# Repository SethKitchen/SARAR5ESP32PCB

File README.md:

# SARAR5ESP32PCB
An IoT PCB integrating the ESP32 and ublox SARA-R5 . Allows for 5G Cellular, Wi-Fi, and Bluetooth in the same device with low form-factor.

This was an open source contibution sponsored by @hiperionio . Thanks so much! If you like what I'm doing please consider sponsoring as well!

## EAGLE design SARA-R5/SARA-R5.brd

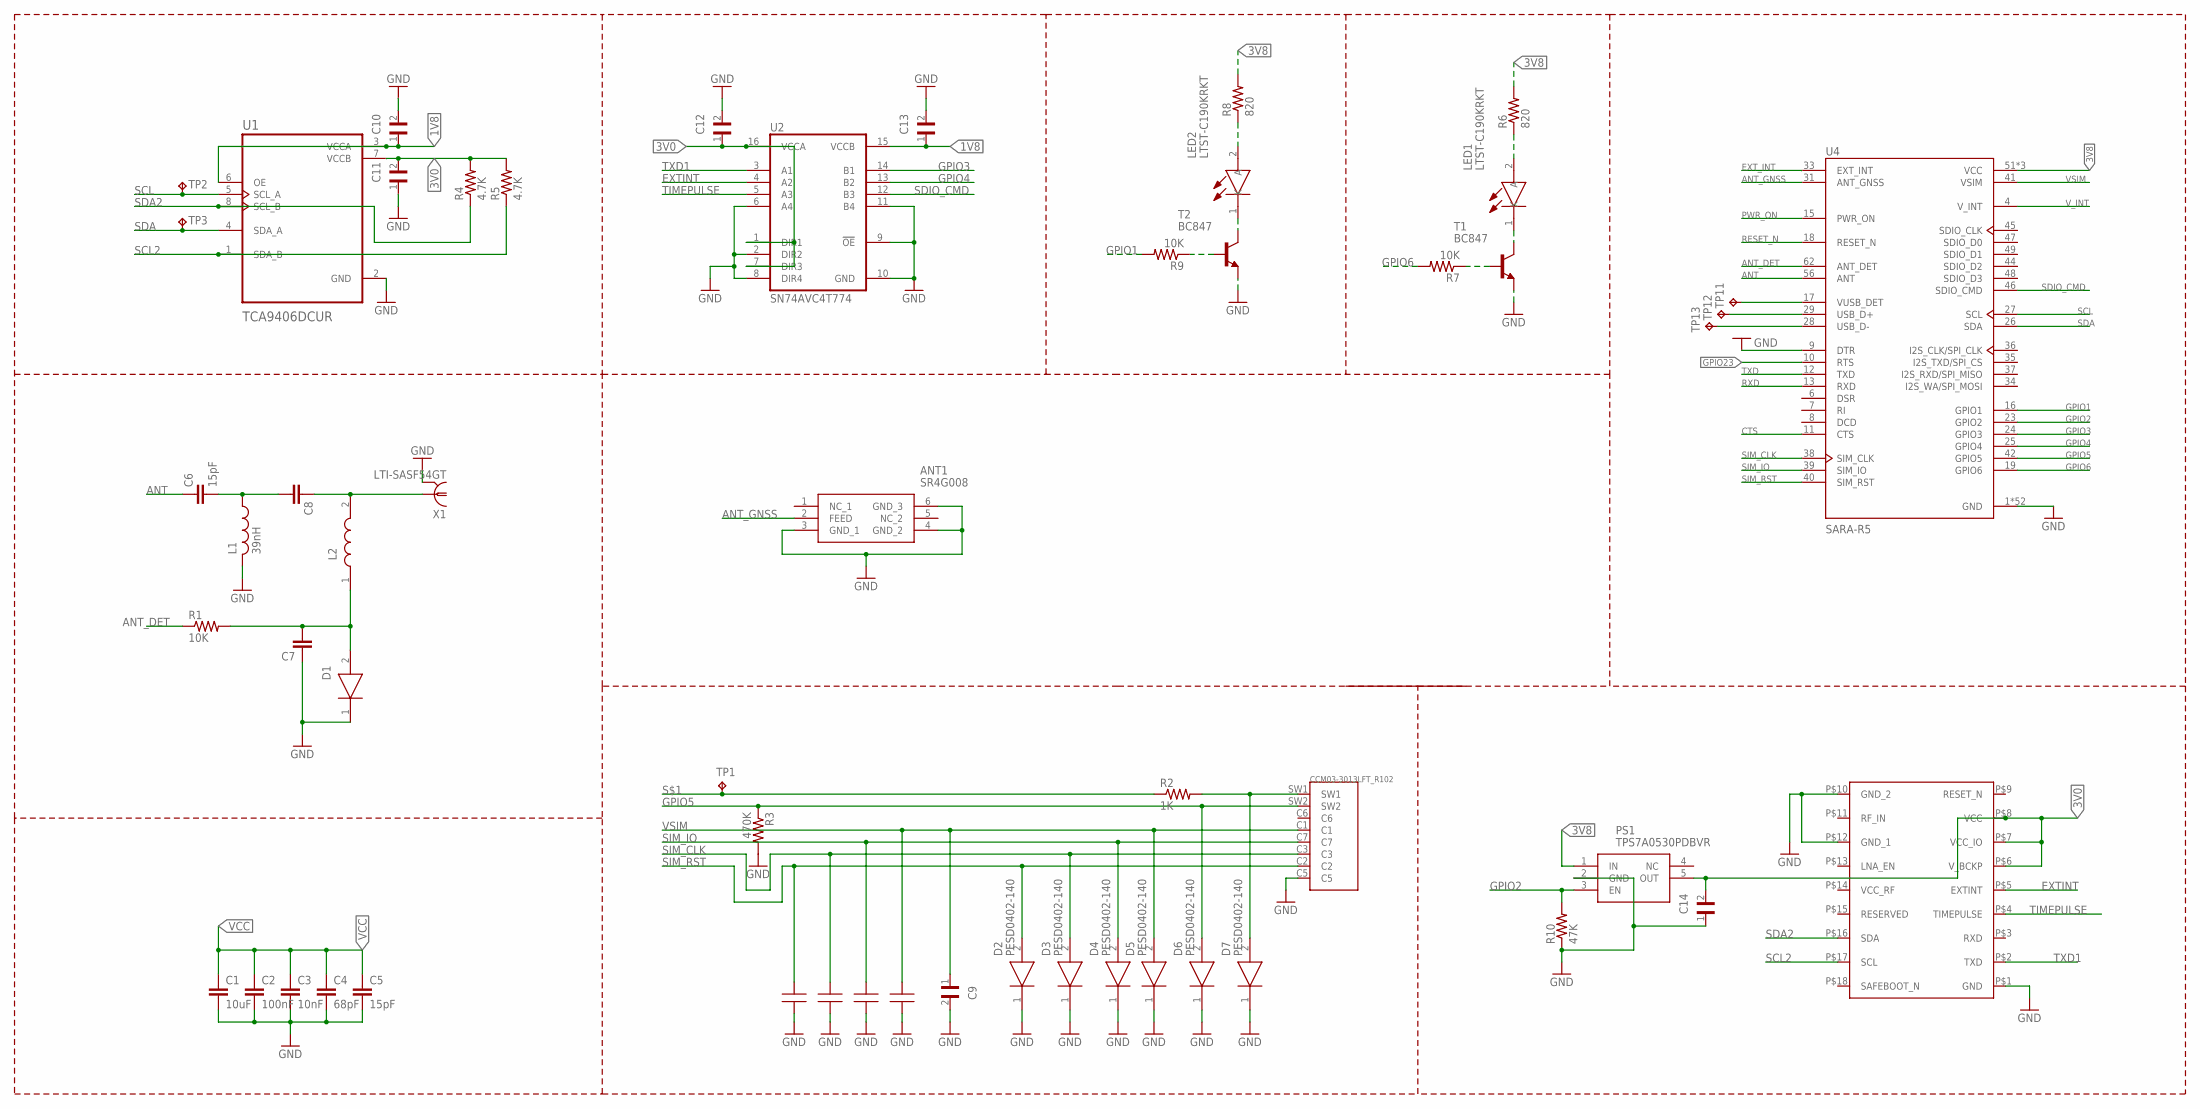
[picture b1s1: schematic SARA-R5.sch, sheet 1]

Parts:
ANT1: SR4G008
C1: 10uF; C0402
C2: 100nF; C0402
C3: 10nF; C0402
C4: 68pF; C0402
C5, C6: 15pF; C0402
C7: 27pF GRM1555C1H270JA16; C0402
C8: 33pF GRM1555C1H330JA16; C0402
C9, C10, C11, C12, C13, C14: GCM155R71C104KA55J; CAPC1005X55N
D1, D2, D3, D4, D5, D6, D7: PESD0402-140; DIONC1005X43N
L1: 39nH; L0402
L2: LQG15HS68NJ02B; LQG15WH0N7B02D
LED1, LED2: LTST-C190KRKT; LEDC1608X80N
PS1: TPS7A0530PDBVR; SOT95P280X145-5N
R1, R7, R9: 10K; R0402
R2: 1K; R0402
R3: 470K; R0402
R4, R5: 4.7K; R0402
R6, R8: 820; R0402
R10: 47K; R0402
T1, T2: BC847; SOT23
TP1: TPB2,54; B2,54
TP2, TP3, TP11, TP12, TP13: TPB1,27; B1,27
U1: TCA9406DCUR; SOP50P310X90-8N
U2: SN74AVC4T774; TSSOP16
U4: SARA-R5
U$1, U$2, U$3, U$4: GRM1555C1E680JA01; INDC1005X45
U$5: MAX-8
X1: LTI-SASF54GT
X2: CCM03-3013LFT_R102; C&K_CCM03-3013LFTR102

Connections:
1V8: C10.1, C13.1, U1.3 (VCCA), U1.6 (OE), U2.15 (VCCB)
3V0: C11.2, C12.1, C14.2, PS1.5 (OUT), R4.2, R5.2, U1.7 (VCCB), U2.1 (DIR1), U2.7 (DIR3), U2.16 (VCCA), U$5.P$6 (V_BCKP), U$5.P$7 (VCC_IO), U$5.P$8 (VCC)
3V8: PS1.1 (IN), R6.2, R8.2, U4.51 (VCC), U4.52 (VCC), U4.53 (VCC)
ANT: C6.1, U4.56 (ANT)
ANT_DET: R1.1, U4.62 (ANT_DET)
ANT_GNSS: ANT1.2 (FEED), U4.31 (ANT_GNSS)
CTS: U4.11 (CTS); also elsewhere on the board
EXTINT: U2.4 (A2), U$5.P$5 (EXTINT)
EXT_INT: U4.33 (EXT_INT)
GND: ANT1.3 (GND_1), ANT1.4 (GND_2), ANT1.6 (GND_3), C1.2, C2.2, C3.2, C4.2, C5.2, C7.1, C9.2, C10.2, C11.1, C12.2, C13.2, C14.1, D1.1 (K), D2.1 (K), D3.1 (K), D4.1 (K), D5.1 (K), D6.1 (K), D7.1 (K), L1.2, PS1.2 (GND), R3.2, R10.1, T1.2 (E), T2.2 (E), U1.2 (GND), U2.2 (DIR2), U2.6 (A4), U2.8 (DIR4), U2.9 (!OE!), U2.10 (GND), U2.11 (B4), U4.1 (GND), U4.3 (GND), U4.5 (GND), U4.9 (DTR), U4.14 (GND), U4.20 (GND), U4.21 (GND), U4.22 (GND), U4.30 (GND), U4.32 (GND), U4.43 (GND), U4.50 (GND), U4.54 (GND), U4.55 (GND), U4.57 (GND), U4.58 (GND), U4.59 (GND), U4.60 (GND), U4.61 (GND), U4.63 (GND), U4.64 (GND), U4.65 (GND), U4.66 (GND), U4.67 (GND), U4.68 (GND), U4.69 (GND), U4.70 (GND), U4.71 (GND), U4.72 (GND), U4.73 (GND), U4.74 (GND), U4.75 (GND), U4.76 (GND), U4.77 (GND), U4.78 (GND), U4.79 (GND), U4.80 (GND), U4.81 (GND), U4.82 (GND), U4.83 (GND), U4.84 (GND), U4.85 (GND), U4.86 (GND), U4.87 (GND), U4.88 (GND), U4.89 (GND), U4.90 (GND), U4.91 (GND), U4.92 (GND), U4.93 (GND), U4.94 (GND), U4.95 (GND), U4.96 (GND), U$1.2, U$2.2, U$3.2, U$4.2, U$5.P$1 (GND), U$5.P$10 (GND_2), U$5.P$12 (GND_1), X1.2, X1.3 (2), X1.4 (2), X1.5 (2), X2.C5; also elsewhere on the board
GPIO1: R9.2, U4.16 (GPIO1)
GPIO2: PS1.3 (EN), R10.2, U4.23 (GPIO2)
GPIO3: U2.14 (B1), U4.24 (GPIO3)
GPIO4: U2.13 (B2), U4.25 (GPIO4)
GPIO5: D6.2 (A), R3.1, U4.42 (GPIO5), X2.SW2
GPIO6: R7.2, U4.19 (GPIO6)
GPIO23: U4.10 (RTS); also elsewhere on the board
unnamed: C7.2, D1.2 (A), L2.1, R1.2
unnamed: C6.2, C8.2, L1.1
unnamed: D7.2 (A), R2.2, X2.SW1
unnamed: LED1.2 (A), R6.1
unnamed: C8.1, L2.2, X1.1
unnamed: LED1.1 (K), T1.3 (C)
unnamed: R7.1, T1.1 (B)
unnamed: LED2.2 (A), R8.1
unnamed: LED2.1 (K), T2.3 (C)
unnamed: R9.1, T2.1 (B)
unnamed: TP11.TP, U4.17 (VUSB_DET)
unnamed: TP12.TP, U4.29 (USB_D+)
unnamed: TP13.TP, U4.28 (USB_D-)
PWR_ON: U4.15 (PWR_ON); also elsewhere on the board
RESET_N: U4.18 (RESET_N); also elsewhere on the board
RXD: U4.13 (RXD); also elsewhere on the board
S$1: R2.1, TP1.TP
SCL: TP2.TP, U1.5 (SCL_A), U4.27 (SCL)
SCL2: R5.1, U1.1 (SDA_B), U$5.P$17 (SCL)
SDA: TP3.TP, U1.4 (SDA_A), U4.26 (SDA)
SDA2: R4.1, U1.8 (SCL_B), U$5.P$16 (SDA)
SDIO_CMD: U2.12 (B3), U4.46 (SDIO_CMD)
SIM_CLK: D3.2 (A), U4.38 (SIM_CLK), U$2.1, X2.C3
SIM_IO: D4.2 (A), U4.39 (SIM_IO), U$3.1, X2.C7
SIM_RST: D2.2 (A), U4.40 (SIM_RST), U$1.1, X2.C2
TIMEPULSE: U2.5 (A3), U$5.P$4 (TIMEPULSE)
TXD: U4.12 (TXD); also elsewhere on the board
TXD1: U2.3 (A1), U$5.P$2 (TXD)
VCC: C1.1, C2.1, C3.1, C4.1, C5.1
VSIM: C9.1, D5.2 (A), U4.41 (VSIM), U$4.1, X2.C1
V_INT: U4.4 (V_INT)

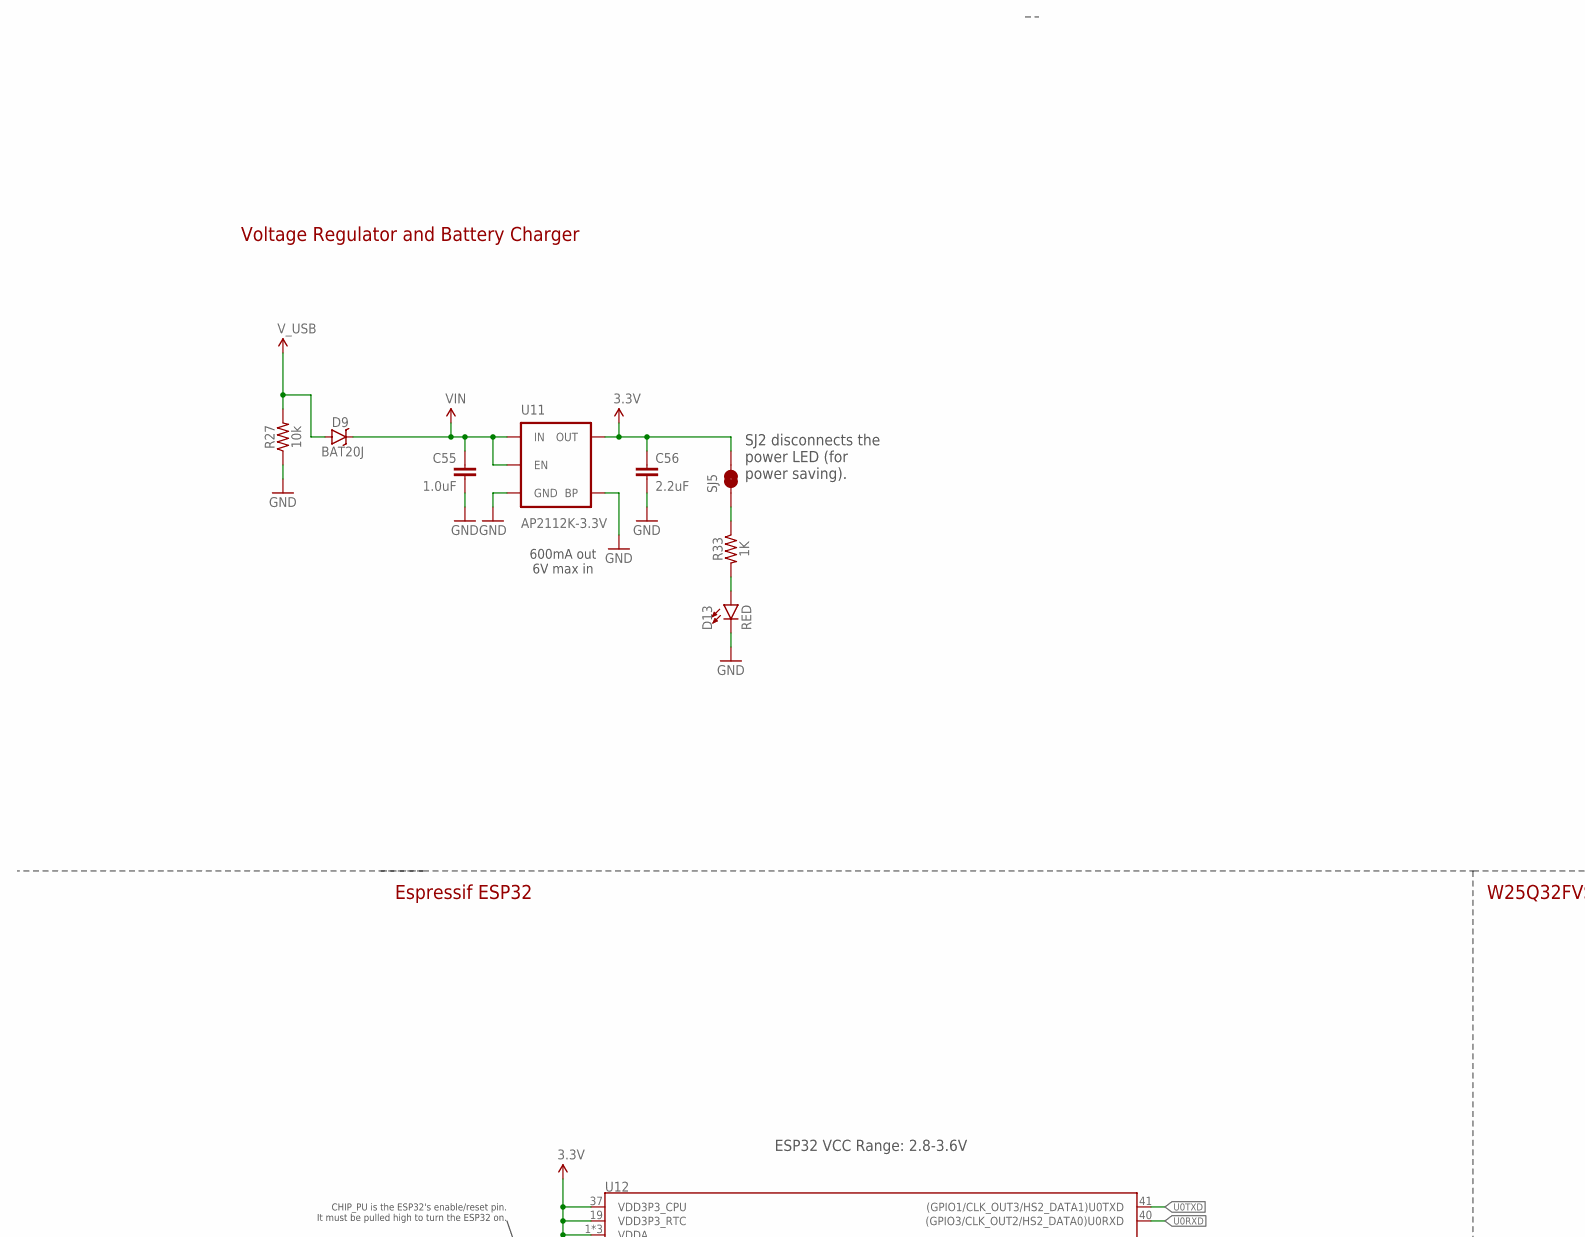
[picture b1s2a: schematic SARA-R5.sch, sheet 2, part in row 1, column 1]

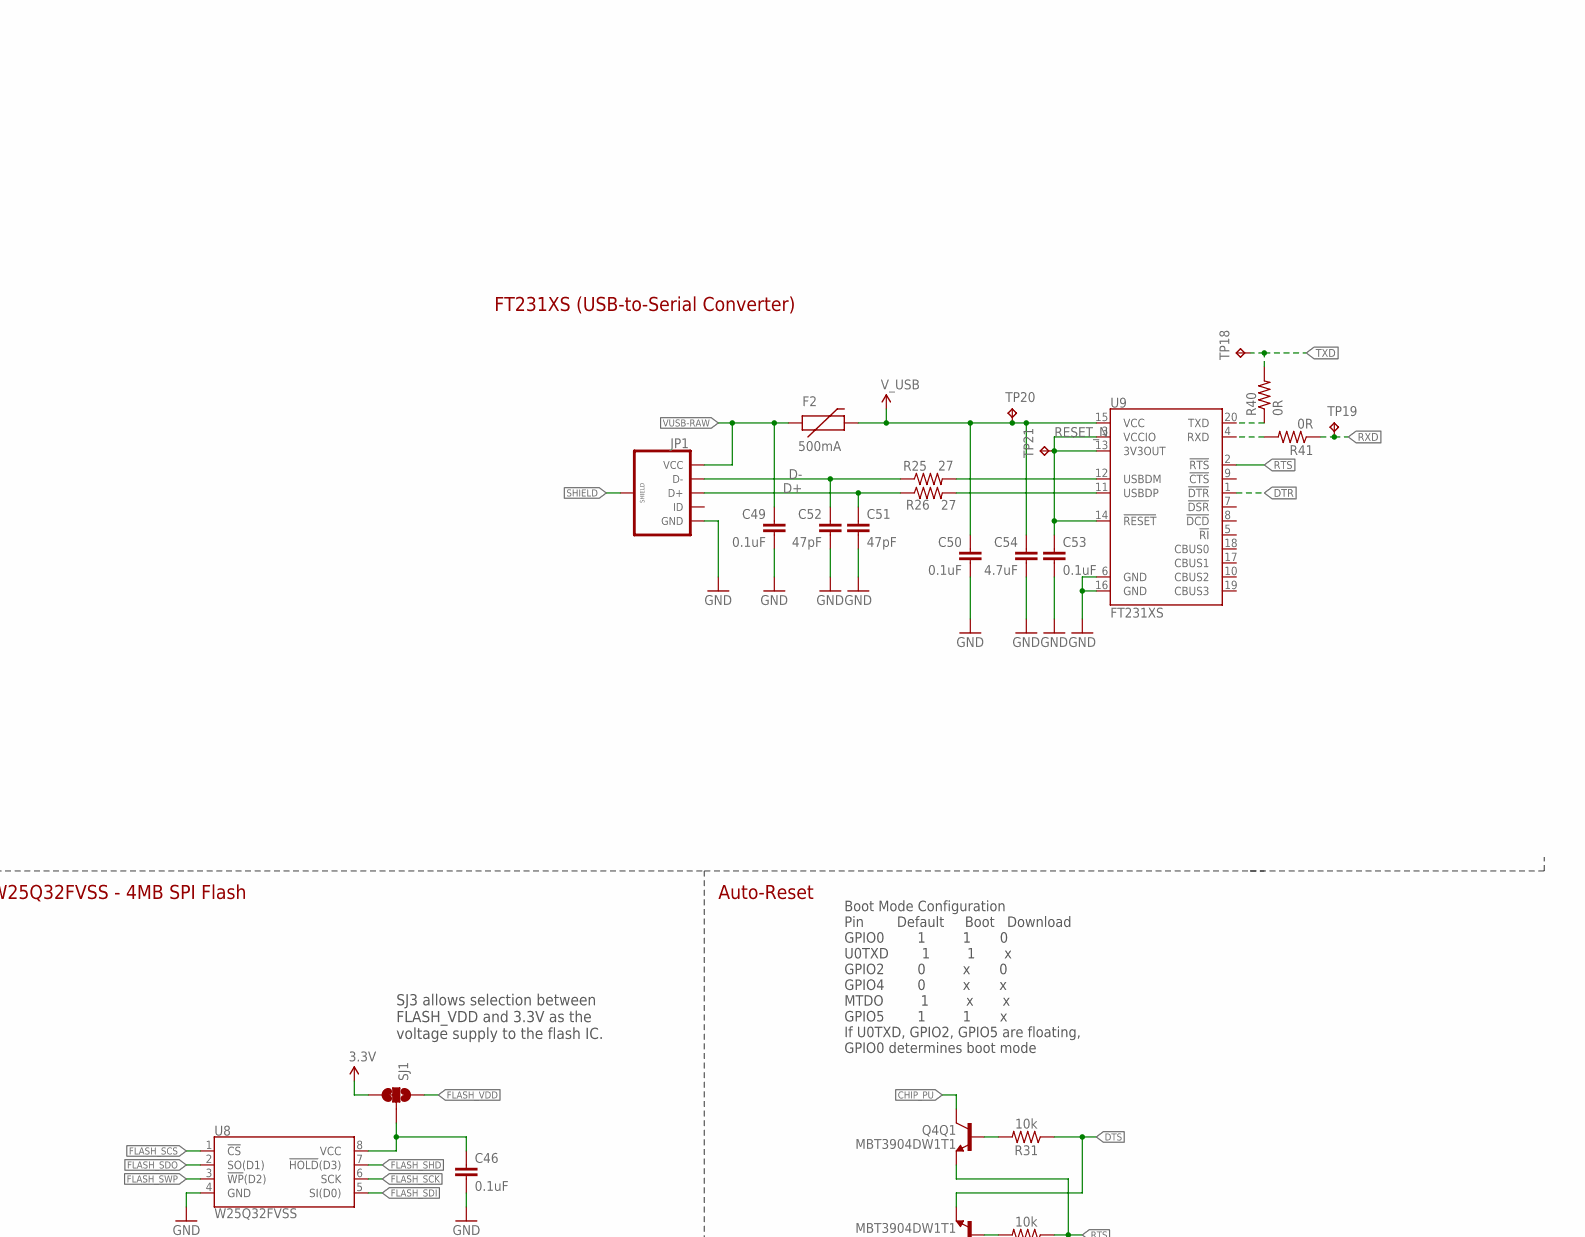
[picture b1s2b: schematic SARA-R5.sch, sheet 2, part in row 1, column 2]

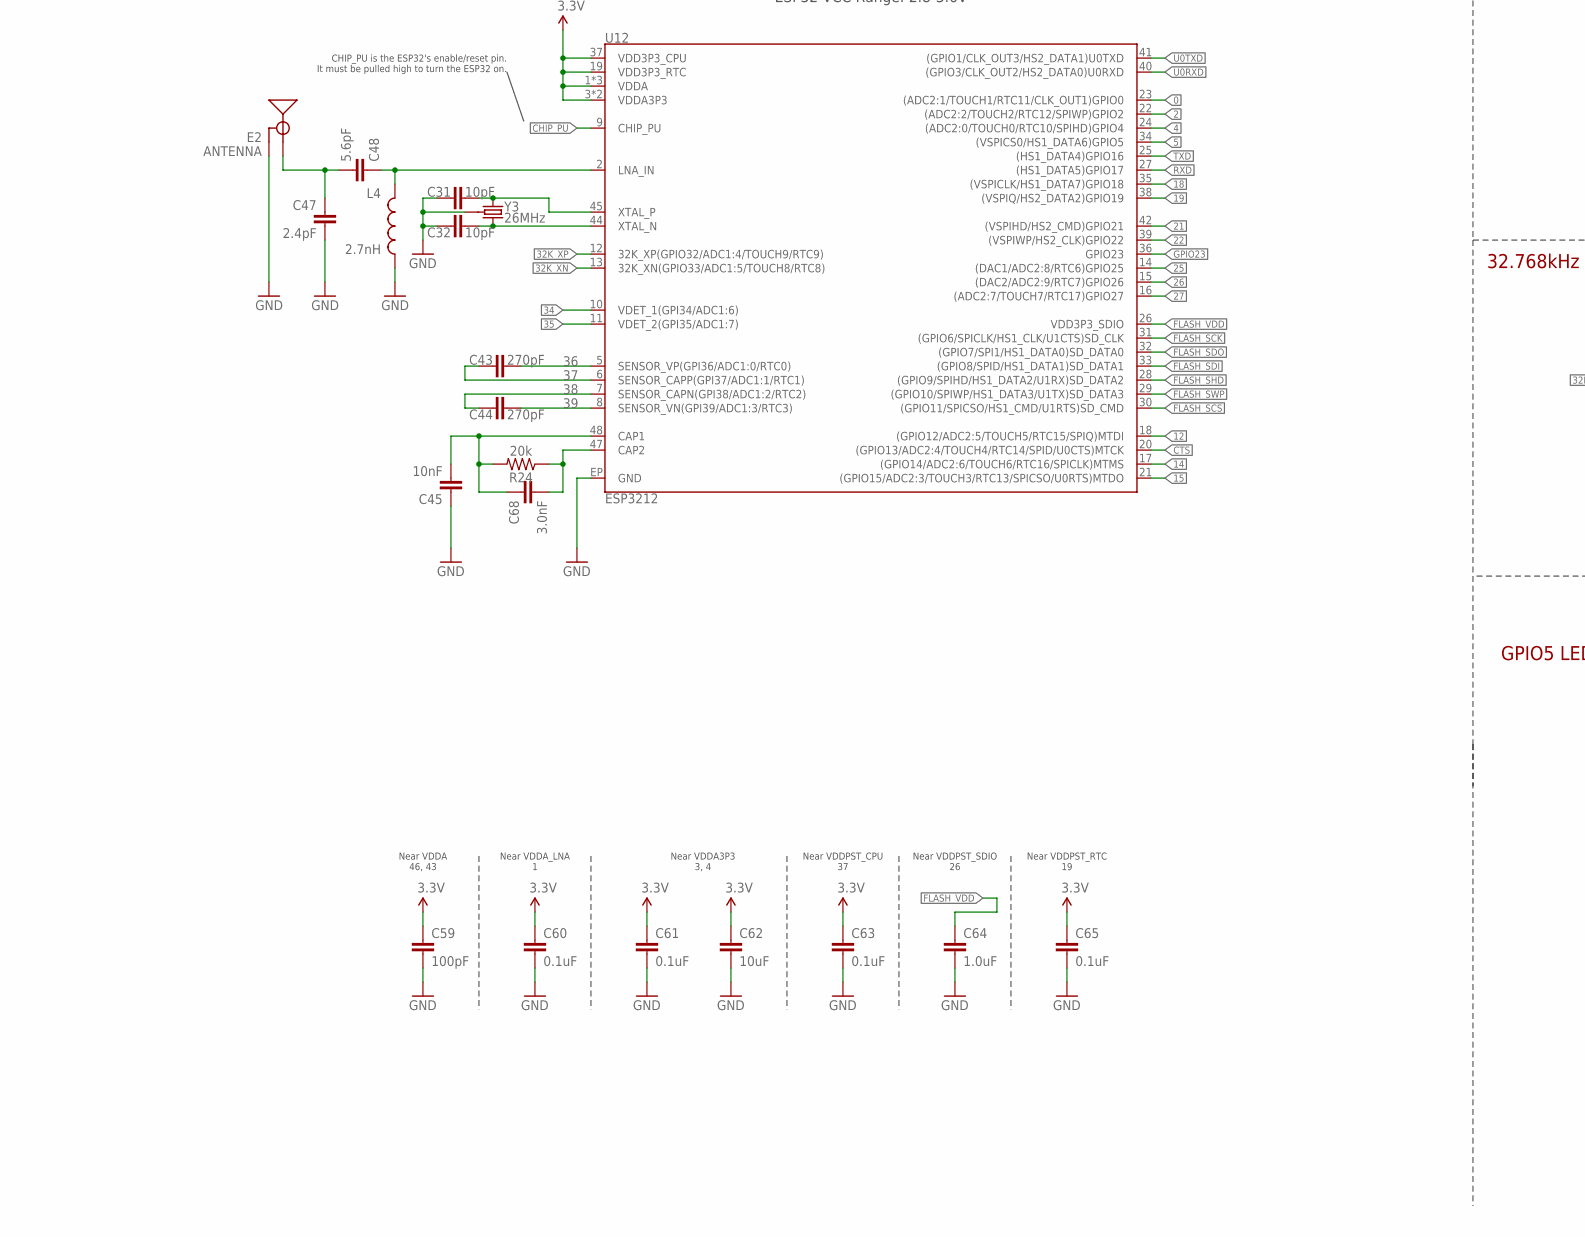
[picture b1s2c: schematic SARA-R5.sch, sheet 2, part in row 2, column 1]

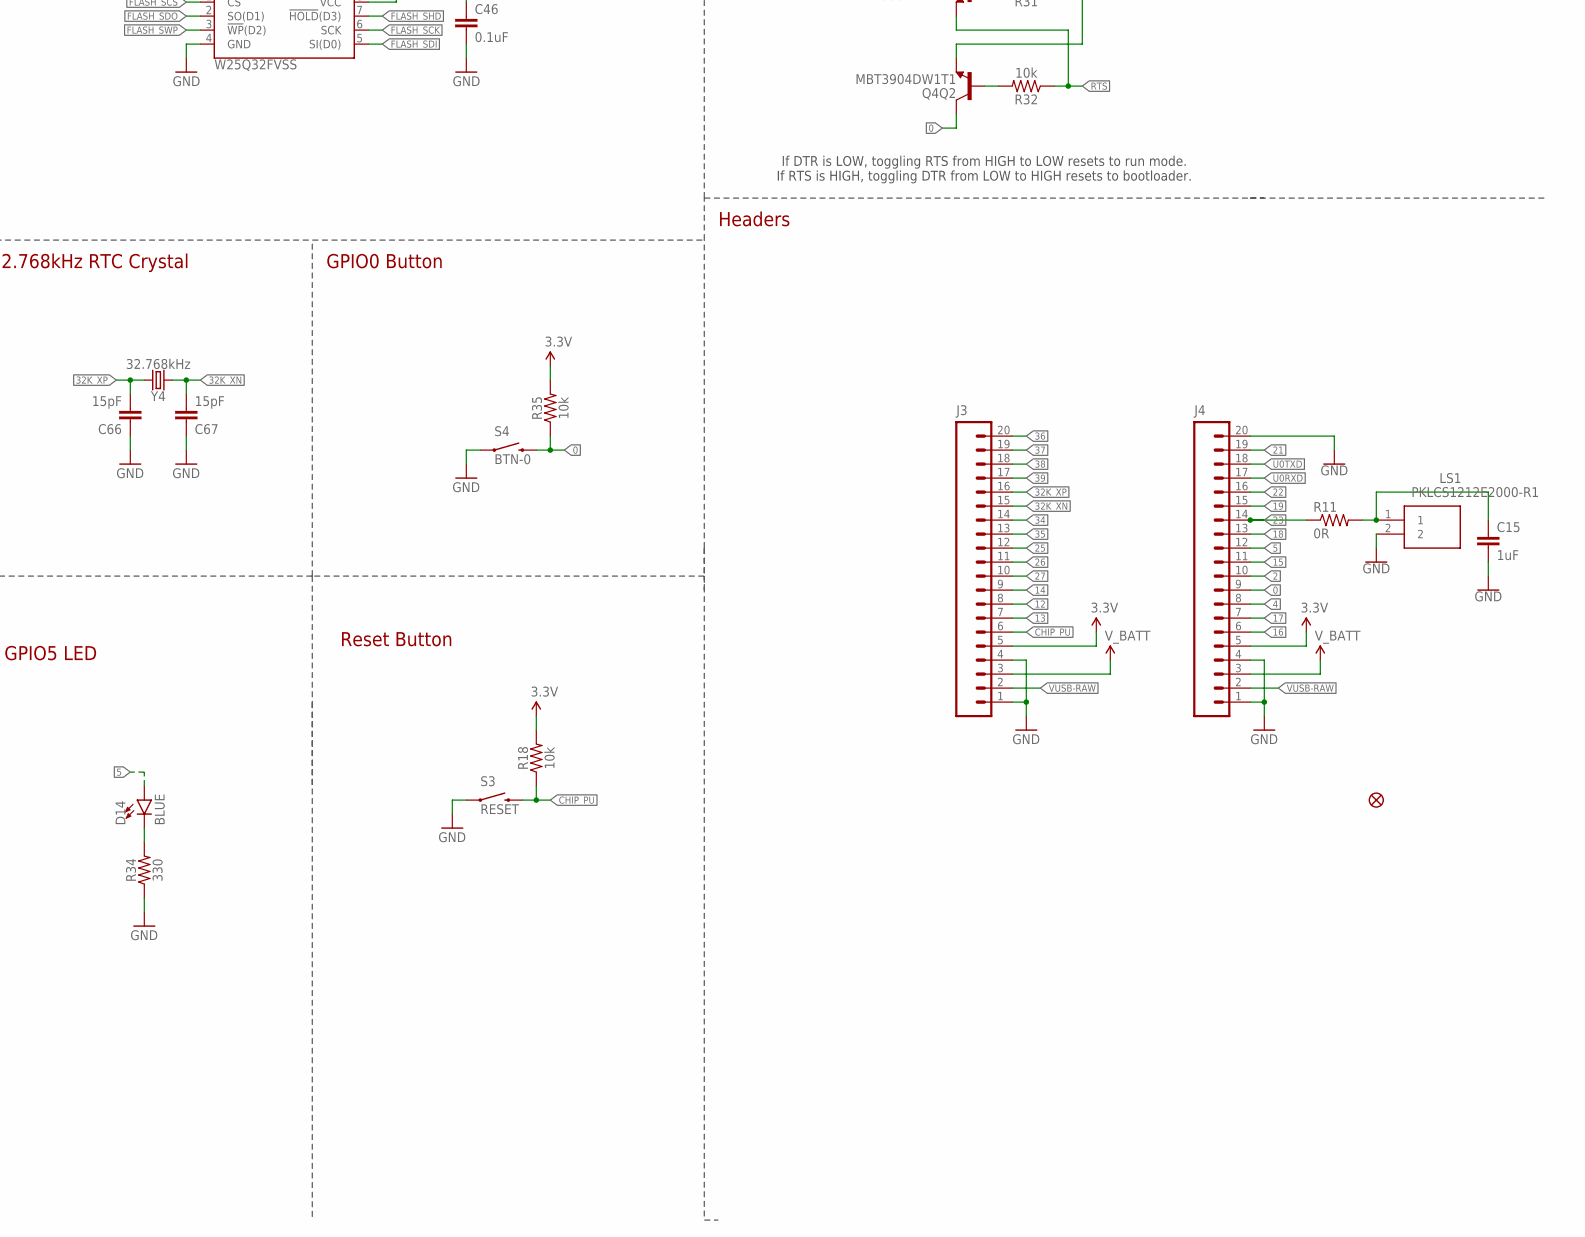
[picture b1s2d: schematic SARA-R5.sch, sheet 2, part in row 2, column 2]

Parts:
C15: 1uF; C0402
C31, C32: 10pF; 0603
C43, C44: 270pF; 0603
C45: 10nF; 0603
C46, C49, C50, C53, C60, C61, C63, C65: 0.1uF; 0603
C47: 2.4pF; 0603
C48: 5.6pF; 0603
C51, C52: 47pF; 0603
C54: 4.7uF; 0603-CAP
C55: 1.0uF; 0805
C56: 2.2uF; 0603
C59: 100pF; 0603
C62: 10uF; 0603
C64: 1.0uF; 0603
C66, C67: 15pF; 0603
C68: 3.0nF; 0603
D9: BAT20J; SOD-323
D13: RED; LED-0603
D14: BLUE; LED-0603
E2: ANTENNA; TRACE_ANTENNA_2.4GHZ_25.7MM_TUNED
F2: 500mA; PTC-1206
FD3: FIDUCIALUFIDUCIAL; MICRO-FIDUCIAL
J3, J4: M20NOSILK; 1X20_NOSILK
JP1: USB_MICROB_PLUGCONN-11752; USB-B-MICRO-SMD_V03
L4: 2.7nH; 0603
LS1: PKLCS1212E2000-R1
Q4: MBT3904DW1T1; SC70-6
R11, R40, R41: 0R; R0402
R18, R27, R31, R32, R35: 10k; 0603
R24: 20k; 0603
R25, R26: 27; 0603
R33: 1K; 0603
R34: 330; 0603
S3: RESET; TACTILE_SWITCH_SMD_4.6X2.8MM
S4: BTN-0; TACTILE_SWITCH_SMD_4.6X2.8MM
SJ1: JUMPER-PAD-3-2OF3_NC_BY_TRACE_SMALL; PAD-JUMPER-3-2OF3_NC_BY_TRACE_YES_SILK_FULL_BOX
SJ5: JUMPER-PAD-2-NC_BY_TRACE; PAD-JUMPER-2-NC_BY_TRACE_YES_SILK
TP18, TP19, TP20, TP21: TPB1,27; B1,27
U8: W25Q32FVSS; SOIC-8
U9: FT231XS; SSOP20_L
U11: AP2112K-3.3V; SOT23-5
U12: ESP3212; QFN48-0.4MM
Y3: 26MHz; CRYSTAL-SMD-3.2X2.5
Y4: 32.768kHz; CRYSTAL-SMD-3.2X1.5MM

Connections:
0: J4.9, Q4.6 (C), R35.1, S4.3 (2), S4.4 (2), U12.23 ((ADC2:1/TOUCH1/RTC11/CLK_OUT1)GPIO0)
2: J4.10, U12.22 ((ADC2:2/TOUCH2/RTC12/SPIWP)GPIO2)
3.3V: C56.1, C59.1, C60.1, C61.1, C62.1, C63.1, C65.1, J3.5, J4.5, R18.2, R35.2, SJ1.3, SJ5.2, U11.5 (OUT), U12.1 (VDDA), U12.3 (VDDA3P3), U12.4 (VDDA3P3), U12.19 (VDD3P3_RTC), U12.37 (VDD3P3_CPU), U12.43 (VDDA), U12.46 (VDDA)
4: J4.8, U12.24 ((ADC2:0/TOUCH0/RTC10/SPIHD)GPIO4)
5: D14.A, J4.12, U12.34 ((VSPICS0/HS1_DATA6)GPIO5)
12: J3.8, U12.18 ((GPIO12/ADC2:5/TOUCH5/RTC15/SPIQ)MTDI)
13: J3.7
14: J3.9, U12.17 ((GPIO14/ADC2:6/TOUCH6/RTC16/SPICLK)MTMS)
15: J4.11, U12.21 ((GPIO15/ADC2:3/TOUCH3/RTC13/SPICSO/U0RT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)
16: J4.6
17: J4.7
18: J4.13, U12.35 ((VSPICLK/HS1_DATA7)GPIO18)
19: J4.15, U12.38 ((VSPIQ/HS2_DATA2)GPIO19)
21: J4.19, U12.42 ((VSPIHD/HS2_CMD)GPIO21)
22: J4.16, U12.39 ((VSPIWP/HS2_CLK)GPIO22)
23: C15.1, J4.14, LS1.1, R11.1, R11.2
25: J3.12, U12.14 ((DAC1/ADC2:8/RTC6)GPIO25)
26: J3.11, U12.15 ((DAC2/ADC2:9/RTC7)GPIO26)
27: J3.10, U12.16 ((ADC2:7/TOUCH7/RTC17)GPIO27)
32K_XN: C67.2, J3.15, U12.13 (32K_XN(GPIO33/ADC1:5/TOUCH8/RTC8)), Y4.P$2 (2)
32K_XP: C66.2, J3.16, U12.12 (32K_XP(GPIO32/ADC1:4/TOUCH9/RTC9)), Y4.P$1 (1)
34: J3.14, U12.10 (VDET_1(GPI34/ADC1:6))
35: J3.13, U12.11 (VDET_2(GPI35/ADC1:7))
36: C43.2, J3.20, U12.5 (SENSOR_VP(GPI36/ADC1:0/RTC0))
37: C43.1, J3.19, U12.6 (SENSOR_CAPP(GPI37/ADC1:1/RTC1))
38: C44.1, J3.18, U12.7 (SENSOR_CAPN(GPI38/ADC1:2/RTC2))
39: C44.2, J3.17, U12.8 (SENSOR_VN(GPI39/ADC1:3/RTC3))
CAP_10N1: C45.2, C68.1, R24.2, U12.48 (CAP1)
CHIP_PU: J3.6, Q4.3 (C), R18.1, S3.3 (2), S3.4 (2), U12.9 (CHIP_PU)
CTS: U12.20 ((GPIO13/ADC2:4/TOUCH4/RTC14/SPID/U0CTS)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); also elsewhere on the board
D+: C51.1, JP1.D+, R26.1
D-: C52.1, JP1.D-, R25.1
DTR: U9.1 (!DTR)
DTS: Q4.1 (E), R31.1
FLASH_SCK: U8.6 (SCK), U12.31 ((GPIO6/SPICLK/HS1_CLK/U1CTS)SD_CLK)
FLASH_SCS: U8.1 (!CS!), U12.30 ((GPIO11/SPICSO/HS1_CMD/U1RTS)SD_CMD)
FLASH_SDI: U8.5 (SI(D0)), U12.33 ((GPIO8/SPID/HS1_DATA1)SD_DATA1)
FLASH_SDO: U8.2 (SO(D1)), U12.32 ((GPIO7/SPI1/HS1_DATA0)SD_DATA0)
FLASH_SHD: U8.7 (!HOLD!(D3)), U12.28 ((GPIO9/SPIHD/HS1_DATA2/U1RX)SD_DATA2)
FLASH_SWP: U8.3 (!WP!(D2)), U12.29 ((GPIO10/SPIWP/HS1_DATA3/U1TX)SD_DATA3)
FLASH_VDD: C64.1, SJ1.1, U12.26 (VDD3P3_SDIO)
GND: C15.2, C31.1, C32.1, C45.1, C46.2, C47.2, C49.2, C50.2, C51.2, C52.2, C53.2, C54.2, C55.2, C56.2, C59.2, C60.2, C61.2, C62.2, C63.2, C64.2, C65.2, C66.1, C67.1, D13.C, E2.GND, E2.GND2 (GND), J3.1, J3.4, J4.1, J4.4, J4.20, JP1.GND, L4.2, LS1.2, R27.1, R34.1, S3.1, S3.2 (1), S4.1, S4.2 (1), U8.4 (GND), U9.6 (GND), U9.16 (GND), U11.2 (GND), U11.4 (BP), U12.EP (GND), Y3.2 (GND), Y3.4 (GND); also elsewhere on the board
GPIO23: U12.36 (GPIO23); also elsewhere on the board
LNA_IN1: C48.1, L4.1, U12.2 (LNA_IN)
unnamed: C46.1, SJ1.2, U8.8 (VCC)
unnamed: R25.2, U9.12 (USBDM)
unnamed: R26.2, U9.11 (USBDP)
unnamed: Q4.5 (B), R31.2
unnamed: Q4.2 (B), R32.2
unnamed: C31.2, U12.45 (XTAL_P), Y3.1
unnamed: C32.2, U12.44 (XTAL_N), Y3.3 (2)
unnamed: D13.A, R33.2
unnamed: R33.1, SJ5.1
unnamed: D14.C, R34.2
unnamed: C68.2, R24.1, U12.47 (CAP2)
unnamed: R40.1, U9.20 (TXD)
unnamed: R41.2, U9.4 (RXD)
PWR_ON: C50.1, C54.1, F2.2, TP20.TP, U9.15 (VCC); also elsewhere on the board
RESET_N: C53.1, TP21.TP, U9.3 (VCCIO), U9.13 (3V3OUT), U9.14 (!RESET); also elsewhere on the board
RTS: Q4.4 (E), R32.1, U9.2 (!RTS)
RXD: R41.1, TP19.TP, U12.27 ((HS1_DATA5)GPIO17); also elsewhere on the board
SHIELD: JP1.SHIELD1 (SHIELD), JP1.SHIELD2 (SHIELD), JP1.SHIELD3 (SHIELD)
TRACE_ANT1: C47.1, C48.2, E2.ANT (SIGNAL)
TXD: R40.2, TP18.TP, U12.25 ((HS1_DATA4)GPIO16); also elsewhere on the board
U0RXD: J4.17, U12.40 ((GPIO3/CLK_OUT2/HS2_DATA0)U0RXD)
U0TXD: J4.18, U12.41 ((GPIO1/CLK_OUT3/HS2_DATA1)U0TXD)
VIN: C55.1, D9.C, U11.1 (IN), U11.3 (EN)
VUSB-RAW: C49.1, F2.1, J3.2, J4.2, JP1.VBUS (VCC)
V_BATT: J3.3, J4.3
V_USB: D9.A, R27.2

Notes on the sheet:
Boot Mode Configuration Pin Default Boot Download GPIO0 1 1 0 U0TXD 1 1 x GPIO2 0 x 0 GPIO4 0 x x MTDO 1 x x GPIO5 1 1 x If U0TXD, GPIO2, GPIO5 are floating, GPIO0 determines boot mode
FT231XS (USB-to-Serial Converter)
Voltage Regulator and Battery Charger
600mA out 6V max in
Auto-Reset
Near VDDA 46, 43
Near VDDA_LNA 1
Near VDDA3P3 3, 4
Near VDDPST_CPU 37
Near VDDPST_SDIO 26
Near VDDPST_RTC 19
Espressif ESP32
W25Q32FVSS - 4MB SPI Flash
32.768kHz RTC Crystal
GPIO0 Button
Reset Button
GPIO5 LED
Headers
ESP32 VCC Range: 2.8-3.6V
SJ3 allows selection between FLASH_VDD and 3.3V as the voltage supply to the flash IC.
SJ2 disconnects the power LED (for power saving).
If DTR is LOW, toggling RTS from HIGH to LOW resets to run mode. If RTS is HIGH, toggling DTR from LOW to HIGH resets to bootloader.
CHIP_PU is the ESP32's enable/reset pin. It must be pulled high to turn the ESP32 on.

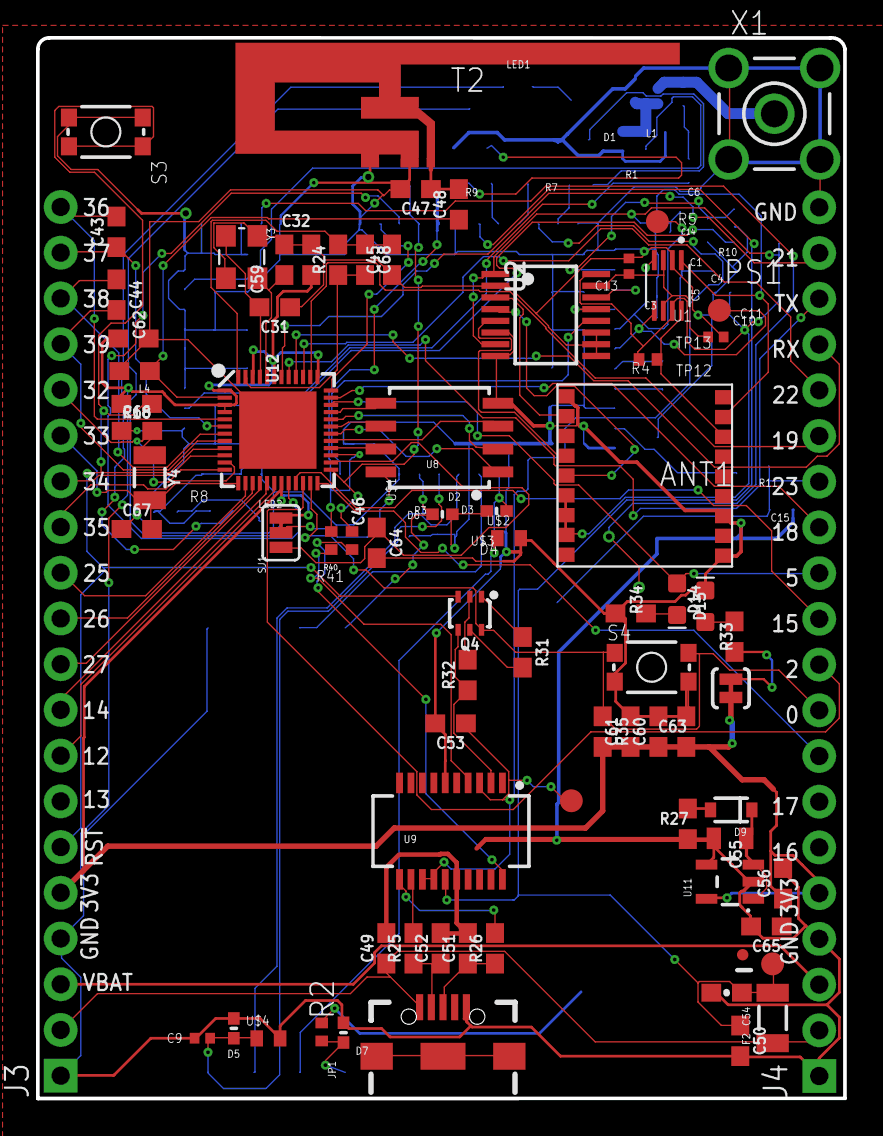
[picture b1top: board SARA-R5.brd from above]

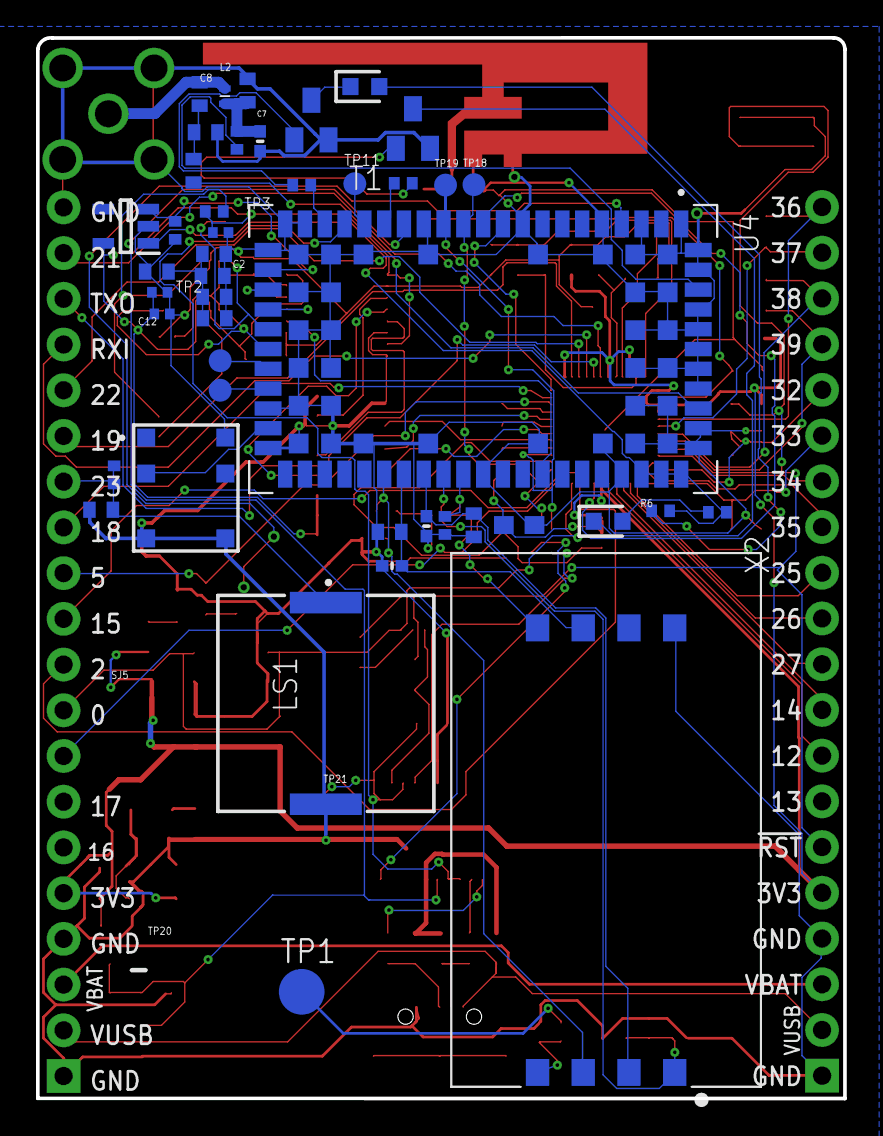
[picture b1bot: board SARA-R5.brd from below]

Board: 2 copper layers, 44.8 x 58.9 mm, 121 parts (44 on the bottom side), 105 nets.

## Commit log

2020-12-15 initial board commit
2020-12-15 add part numbers
2020-12-15 Add Sponsor Recognition

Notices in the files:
parts and their libraries:
SparkFun-Capacitors: Licensing: Creative Commons ShareAlike 4.0 International - https://creativecommons.org/licenses/by-sa/4.0
SparkFun-DigitalIC: Licensing: CC v3.0 Share-Alike You are welcome to use this library for commercial purposes.
